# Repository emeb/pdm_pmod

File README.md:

# pdm_pmod
A stereo headphone driver using Pulse Density Modulation

## Abstract
This project was built as a quick test to check out the concept of a PDM audio
output through a low-voltage headphone driver prior to using it in some more
complex projects. It's a small and simple 4-bit PMOD that won't use up a lot of
your FPGA devboard's I/O and still provides decent-quality stereo audio when
used in conjunction with a low-complexity PMOD gateware which can be found in
other projects in my github account:

## Hardware
The hardware design is provided as schematic and layout in KiCAD 6 format.
The design provides:
* Single-row (4-bit, 6-pin) PMOD connector.
* Stereo 3.5mm TRS headphone jack.

## Gateware
A PDM stereo driver compatible with this can be found here:

https://github.com/emeb/orangecrab_adc/blob/master/gateware/verilog/src/pdm_dac.v

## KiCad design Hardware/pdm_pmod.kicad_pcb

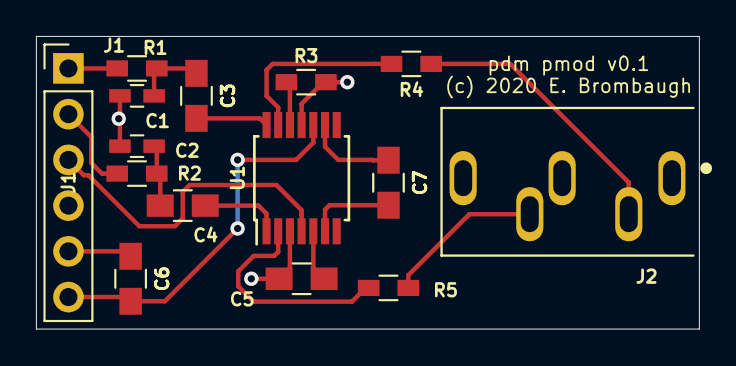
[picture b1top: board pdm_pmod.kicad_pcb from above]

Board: 2 copper layers, 36.8 x 16.3 mm, 15 parts (0 on the bottom side), 17 nets.

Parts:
C1, C2: 0.1uf; C_0603_HandSoldering
C3, C4: 10uf; C_0805_HandSoldering
C5, C6, C7: 1uf; C_0805_HandSoldering
J1: Conn_01x06_Male; Pin_Header_Straight_1x06_Pitch2.54mm
J2: SJ1-3535NG-GR; CUI_SJ1-3535NG-GR
R1, R2: 100; R_0603_HandSoldering
R3: 82K; R_0603_HandSoldering
R4, R5: 470; R_0603_HandSoldering
U1: TPA6139A2; TSSOP-14_4.4x5mm_Pitch0.65mm

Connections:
+3V3: C6.2, J1.6, U1.10
/L_PWM: J1.1, R1.2
/R_PWM: J1.2, R2.2
/nMUTE: J1.3, U1.4
GND: C1.2, C2.2, C5.2, C6.1, J1.5, J2.1, R3.2, U1.3, U1.11
unnamed: C1.1, C3.1, R1.1
unnamed: C2.1, C4.1, R2.1
unnamed: C3.2, U1.14
unnamed: C4.2, U1.1
unnamed: C5.1, U1.5
unnamed: C7.1, U1.9
unnamed: C7.2, U1.6
unnamed: J2.2, R4.1
unnamed: J2.3, R5.1
unnamed: R3.1, U1.12
unnamed: R4.2, U1.13
unnamed: R5.2, U1.2

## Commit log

2022-05-18 Initial checkin of hardware and docs

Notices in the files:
Hardware/pdm_pmod.kicad_pcb:
(c) 2020 E. Brombaugh
